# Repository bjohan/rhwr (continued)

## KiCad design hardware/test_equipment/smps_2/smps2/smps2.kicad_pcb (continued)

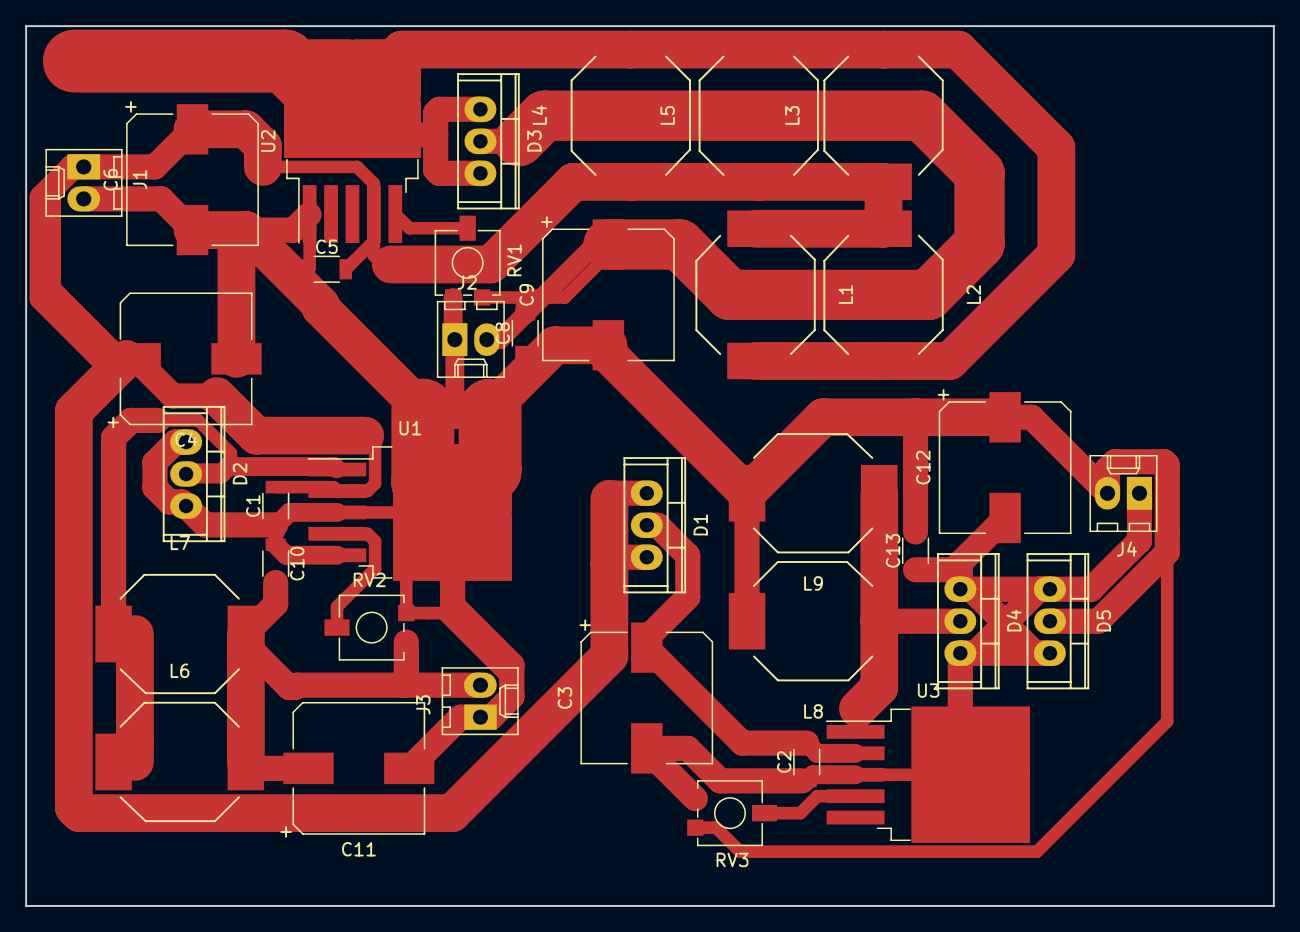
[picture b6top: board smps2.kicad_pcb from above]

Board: 2 copper layers, 99.1 x 69.9 mm, 36 parts (0 on the bottom side), 12 nets.

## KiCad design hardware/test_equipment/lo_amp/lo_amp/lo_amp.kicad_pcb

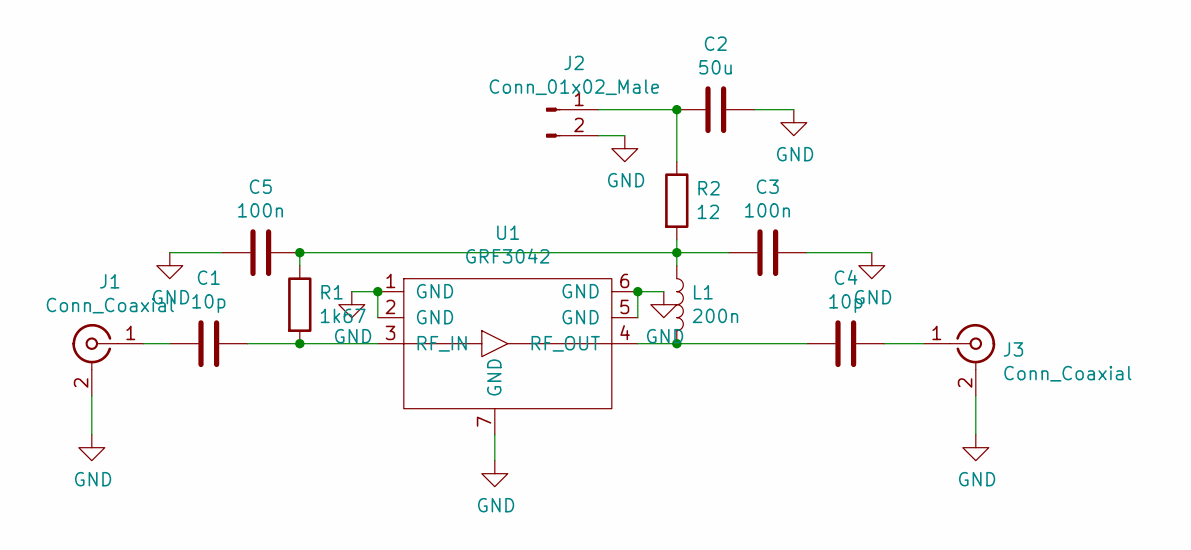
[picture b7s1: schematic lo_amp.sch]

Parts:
C1, C4: 10p; C_0402
C2: 50u; CP_Elec_10x10.5
C3, C5: 100n; C_0402
J1, J3: Conn_Coaxial; Molex_SMA_Jack_Edge_Mount
J2: Conn_01x02_Male; Molex_KK-6410-02_02x2.54mm_Straight
L1: 200n; R_0402
R1: 1k67; R_0402
R2: 12; R_0402
U1: GRF3042; grf3042

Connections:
GND: C2.1, C3.1, C5.2, J1.2 (Ext), J2.2, J3.2 (Ext), U1.1 (GND), U1.2 (GND), U1.5 (GND), U1.6 (GND), U1.7 (GND)
unnamed: C1.1, R1.2, U1.3 (RF_IN)
unnamed: C1.2, J1.1 (In)
unnamed: C2.2, J2.1, R2.1
unnamed: C3.2, C5.1, L1.1, R1.1, R2.2
unnamed: C4.1, J3.1 (In)
unnamed: C4.2, L1.2, U1.4 (RF_OUT)

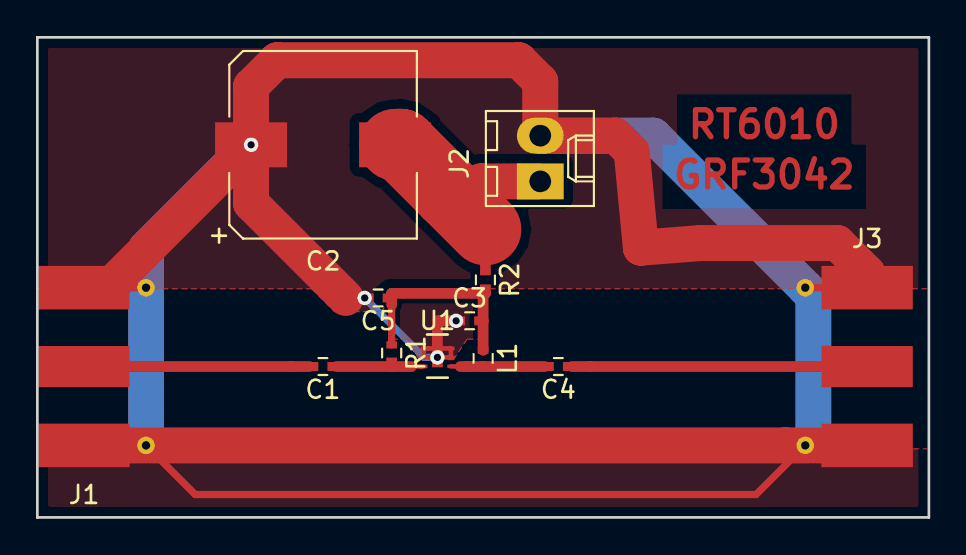
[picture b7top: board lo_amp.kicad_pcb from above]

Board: 2 copper layers, 49.5 x 26.7 mm, 12 parts (0 on the bottom side), 7 nets.

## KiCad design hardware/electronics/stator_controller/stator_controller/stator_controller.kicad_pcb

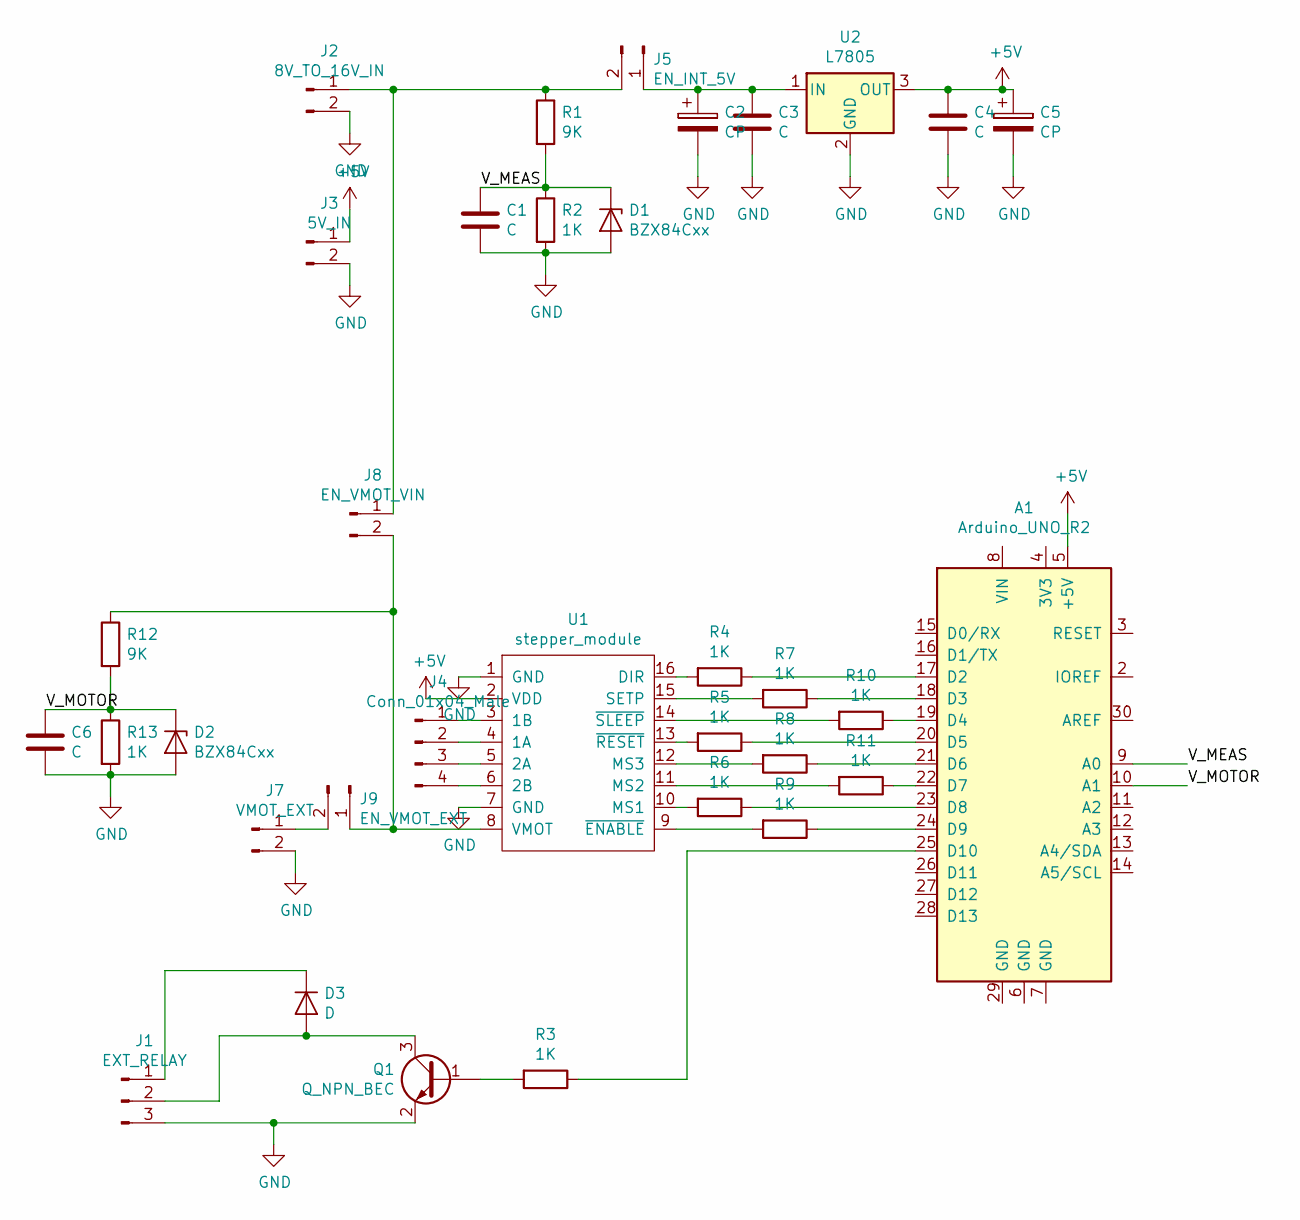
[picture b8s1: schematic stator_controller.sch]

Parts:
A1: Arduino_UNO_R2; Arduino_Uno_Shield
C1, C3, C4, C6: C; C_1206
C2, C5: CP; CP_Elec_10x10.5
D1, D2: BZX84Cxx; D_SOT-23_ANK
D3: D; D_2010
J1: EXT_RELAY; Molex_SPOX-5267_22-03-5035_03x2.54mm_Straight
J2: 8V_TO_16V_IN; PhoenixContact_MSTBVA-G_02x5.08mm_Vertical
J3: 5V_IN; PhoenixContact_MSTBVA-G_02x5.08mm_Vertical
J4: Conn_01x04_Male; Molex_SPOX-5267_22-03-5045_04x2.54mm_Straight
J5: EN_INT_5V; Molex_SPOX-5267_22-03-5025_02x2.54mm_Straight
J7: VMOT_EXT; PhoenixContact_MSTBVA-G_02x5.08mm_Vertical
J8: EN_VMOT_VIN; Molex_SPOX-5267_22-03-5025_02x2.54mm_Straight
J9: EN_VMOT_EXT; Molex_SPOX-5267_22-03-5025_02x2.54mm_Straight
Q1: Q_NPN_BEC; SOT-23
R1, R12: 9K; R_1206
R2, R3, R4, R5, R6, R7, R8, R9, R10, R11, R13: 1K; R_1206
U1: stepper_module; DIP-16_500_ELL
U2: L7805; TO-220

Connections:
+5V: A1.5 (+5V), C4.1, C5.1, J3.1, U1.2 (VDD), U2.3 (OUT)
/V_MEAS: A1.9 (A0), C1.1, D1.1 (K), R1.2, R2.1
/V_MOTOR: A1.10 (A1), C6.1, D2.1 (K), R12.2, R13.1
GND: C1.2, C2.2, C3.2, C4.2, C5.2, C6.2, D1.2 (A), D2.2 (A), J1.3, J2.2, J3.2, J7.2, Q1.2 (E), R2.2, R13.2, U1.1 (GND), U1.7 (GND), U2.2 (GND)
unnamed: A1.17 (D2), R4.1
unnamed: A1.18 (D3), R7.1
unnamed: A1.19 (D4), R10.1
unnamed: A1.20 (D5), R5.1
unnamed: A1.21 (D6), R8.1
unnamed: A1.22 (D7), R11.1
unnamed: A1.23 (D8), R6.1
unnamed: A1.24 (D9), R9.1
unnamed: A1.25 (D10), R3.1
unnamed: C2.1, C3.1, J5.1, U2.1 (IN)
unnamed: D3.1 (K), J1.1
unnamed: D3.2 (A), J1.2, Q1.3 (C)
unnamed: J2.1, J5.2, J8.1, R1.1
unnamed: J4.1, U1.3 (1B)
unnamed: J4.2, U1.4 (1A)
unnamed: J4.3, U1.5 (2A)
unnamed: J4.4, U1.6 (2B)
unnamed: J7.1, J9.2
unnamed: J8.2, J9.1, R12.1, U1.8 (VMOT)
unnamed: Q1.1 (B), R3.2
unnamed: R4.2, U1.16 (DIR)
unnamed: R5.2, U1.13 (~RESET)
unnamed: R6.2, U1.10 (MS1)
unnamed: R7.2, U1.15 (SETP)
unnamed: R8.2, U1.12 (MS3)
unnamed: R9.2, U1.9 (~ENABLE)
unnamed: R10.2, U1.14 (~SLEEP)
unnamed: R11.2, U1.11 (MS2)

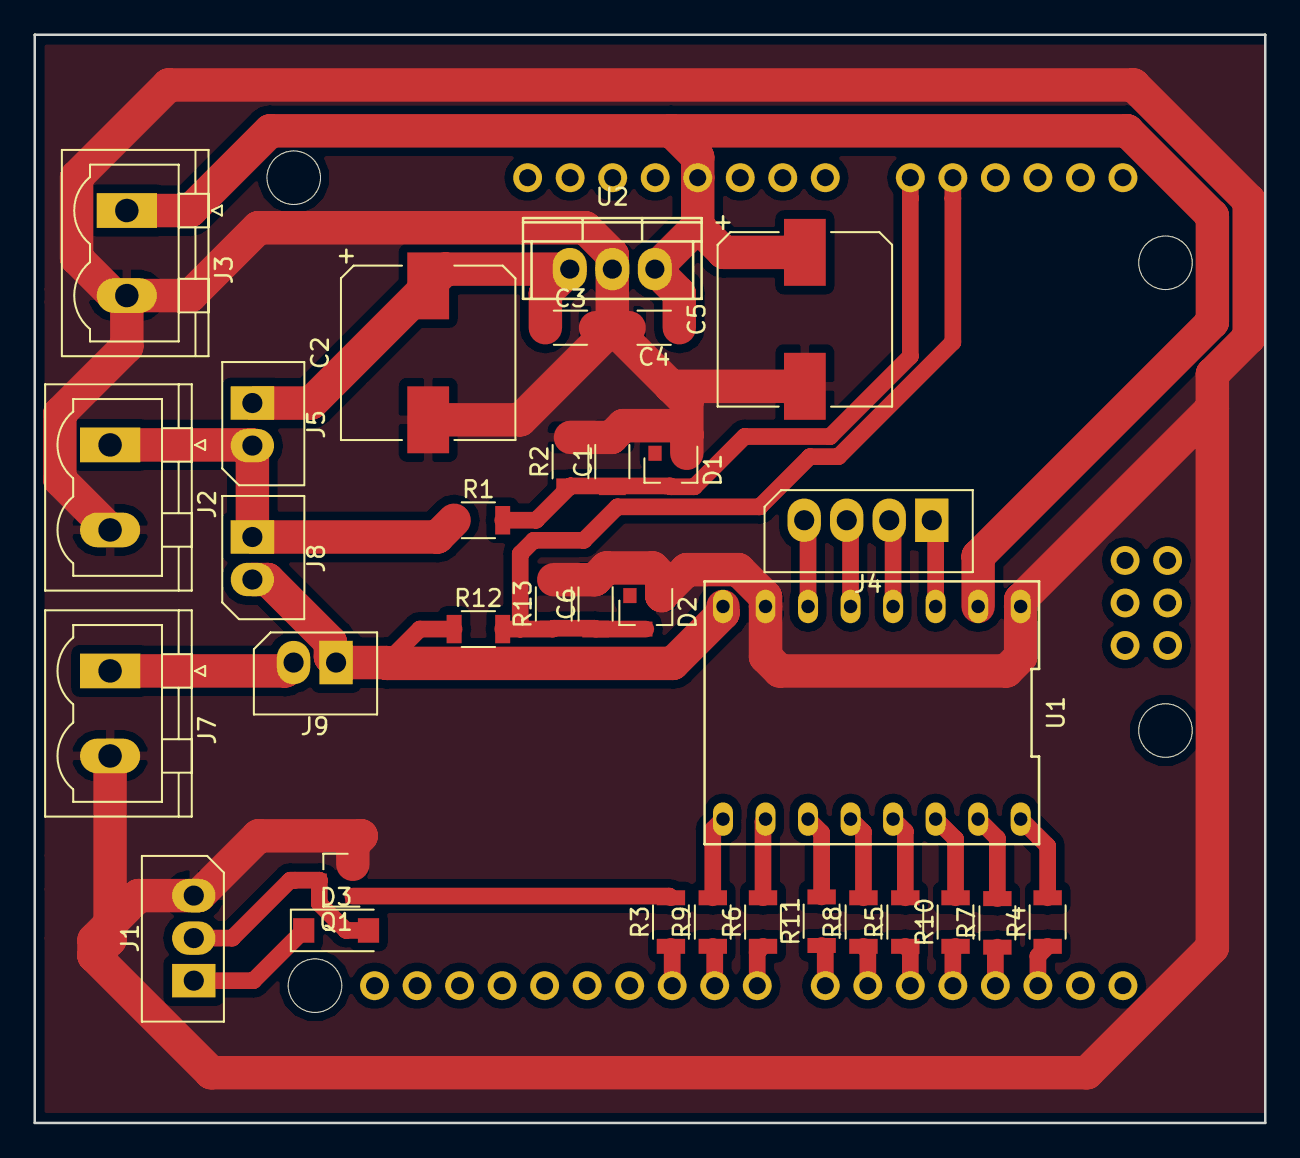
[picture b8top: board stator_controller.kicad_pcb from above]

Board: 2 copper layers, 73.5 x 65.0 mm, 34 parts (1 on the bottom side), 32 nets.

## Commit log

2020-08-16 Added submodule for Corbomite library
2020-08-16 moved dependency
2020-08-16 Added project files
2020-08-16 added submodule
2020-08-16 Started adding lmx interface
2020-08-17 More on control software
2020-08-17 PLL now locks
2020-08-17 Something needs sleep, troubleshoot after sleep...
2020-08-18 Something is not right, pll does not always lock when reading registers....
2020-08-20 Updated system diagram to reflect current hw status
2020-08-24 Fixed pin mappings
2020-08-24 Testing filters and gain in low band receiver
2020-08-25 More testing
2020-09-12 Fixed issue where step pulses stopped being generated for a while, and updated usb port
2020-09-13 Now both pll interfaces seems to work
2020-09-13 Corbomatized turntable sketch
2020-09-15 Started writing more usable receiver controls
2020-09-16 Refactoring and initial turntable code
2020-09-17 Better ramping and sdr-to-gpu-test code
2020-09-18 Used 1/16 microstep to reduce audible noise
2020-10-04 Embryo for signal processing
2020-10-04 Before dividing to smaller files
2020-10-04 Divided in to smaller files
2020-10-04 Started working on class to write samples to gpu
2020-10-04 fixed bug in interthreadbuffer
2020-10-05 Sample buffering now seems to work
2020-10-06 Tested complete chain, receive on higbhand receiver, in through hackrf, in to gpu memory and out from gpu memory in to a plot!
2020-10-10 Started working on tcp interface and signal processing pipeline
2020-10-11 Minor changes to thread queue
2020-10-12 Started working on tcp interface
2020-10-18 Makeing less bad buffers
2020-10-18 Removed unused file
2020-10-18 More buffering related changes
2020-10-18 Removed wrong file
2020-10-18 Started working on data processing flow
2020-10-24 removed file
2020-11-15 Moved hackrf to threads in preparation for interactive console
2020-11-16 stated working on client
2020-11-16 rename
2020-11-16 Now builds two applications
2021-03-24 started working on commandprompt
2021-03-29 Added embryo for command parser
2021-03-30 embryo for server/client
2021-04-02 started working on messaging framework
2021-04-05 print status
2021-04-05 Added small factory class
2021-04-10 Added publish subscribe mechanism, need to make it thread safe
2021-05-02 started adding plot code
2021-05-02 removed som missed objects in make clean
2021-11-28 tcp stuff
2023-01-07 Started working on small sdr application just to have a simpler test bed for signal processing and plotting
2023-01-07 Now rendering teapot
2023-01-08 Simple application working with most of rx chain scaffolding in place
2023-01-10 Made some new derived queue classes
2023-01-22 Started adding nmea gps stuff
2023-01-22 Moved signal processor and started working on signal stacker
